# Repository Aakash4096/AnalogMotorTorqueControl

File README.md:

# Zine Project
## Stage 0:
Downloading application such as KiCAD for designing ,simulation and PCB development for the whole project
### Before going to project, the terms one should be familiar with

H-Bridge	A configuration of four MOSFETs (Q1–Q4) that allows current through a DC motor to flow in both directions. It’s called an “H-bridge” because the circuit looks like the letter H: the motor forms the crossbar, and the transistors form the legs.
Purpose	Used to control both direction and speed of a DC motor.
Operation Modes	- Forward: Q1 + Q4 ON (current one way)
- Reverse: Q2 + Q3 ON (current opposite way)
- Brake: Both high-side ON or both low-side ON
- Coast: All OFF
Control Method	Controlled via PWM (Pulse Width Modulation) to vary speed, and logic signals to change direction.

------------------------------------------------------

Half-Bridge	A circuit that controls one side (or “leg”) of an H-bridge — it has a high-side switch and a low-side switch.
Half-Bridge Driver IC	A chip that generates proper gate voltages to drive both MOSFETs (one high-side and one low-side) safely. Example: IR2104, IR2101, HIP4081.
Need for a Driver	- The high-side MOSFET’s gate needs a voltage higher than the supply (Vcc) to turn fully ON.
- A bootstrap capacitor provides this extra voltage.
- The driver ensures dead-time (short delay between switching) so both MOSFETs are not ON at the same time (which would cause a short).
Full H-Bridge with Drivers	Two half-bridge driver ICs together make a full H-bridge (one IC controls each motor terminal).

-----------------------------------------------------

High-Side Switch	The transistor (MOSFET) that connects the motor terminal to +Vcc (e.g., Q1, Q3). Must handle full supply voltage. Usually a P-channel MOSFET or an N-channel driven by a bootstrap circuit.
Low-Side Switch	The transistor that connects the motor terminal to GND (e.g., Q2, Q4). Driven directly from a logic gate or driver IC.
Challenge	Driving the high-side switch requires a voltage higher than Vcc, which is why driver ICs are essential.

-----------------------------------------------------------------

Definition	A digital control method where you switch the motor ON and OFF rapidly (hundreds or thousands of times per second). The average voltage seen by the motor determines speed.
Duty Cycle	The ratio of ON time to total period. Higher duty cycle → more average voltage → faster motor speed.
Frequency	Typical values: 5–20 kHz (high enough to avoid audible noise).
Implementation	Generated by a microcontroller (in your case, ATtiny13A) and fed to the driver IC inputs.

--------------------------------------------------------------------------

Bootstrap Capacitor (Cboot)	A capacitor charged to Vcc when the low-side switch is ON. When the high-side turns ON, this stored charge provides the extra gate voltage needed.
Bootstrap Diode (Dboot)	Allows the capacitor to charge when the low-side is ON, but blocks discharge.
Purpose	Enables an N-channel MOSFET to be used as a high-side transistor (better efficiency and lower Rds(on) than P-channel).

----------------------------------------------------------------------------

Dead-Time Control:-

Definition-	A short time delay between turning OFF one MOSFET and turning ON the opposite one in the same leg.
Why Needed-	Prevents both high-side and low-side switches from being ON simultaneously → avoids shoot-through current, which can destroy the transistors.
Implementation-	Usually built-in inside driver IC (like IR2104) or added by microcontroller timing logic.

---------------------------------------------------------------------------

Current Sensing and Torque Control-

Current Sense Resistor (Rshunt)	A small resistor (e.g., 0.1 Ω) placed in series with the motor to measure current.
Voltage Drop = I × R	The voltage across this resistor is proportional to the motor current → proportional to torque.
Analog Amplifier	Amplifies this small voltage for ADC measurement by the microcontroller.
Torque Control	By regulating motor current, you effectively control torque output (since torque ∝ current in DC motors).

--------------------------------------------------------------------------------

Protection Components-

Flyback Diodes (D1–D4)	Protect MOSFETs from voltage spikes due to motor’s inductive load when switching. Sometimes intrinsic in MOSFETs.
TVS Diode	Protects against sudden voltage surges from external power supply.
Fuse	Protects from short circuits or motor stall overcurrent.
Decoupling Capacitors (C1, C2, etc.)	Stabilize power lines and reduce switching noise.

-------------------------------------------------------------------------------------

Microcontroller (ATtiny13A)
Role	Explanation         
PWM Generation	Generates PWM signals for speed control.    
Direction Control	Sends logic signals to change motor direction.    
Current Measurement	Reads current sense signal for torque estimation.          
Feedback / Safety	Optionally can stop or limit current if torque too high.        

## Stage 1 – Circuit Design

### Power Stage – H-Bridge Design(Idea From Other's Project)

Purpose:

The H-Bridge is a power control circuit that lets current flow through a motor in both directions, so the motor can rotate clockwise or anticlockwise.
It also helps control speed and torque when used with PWM (Pulse Width Modulation) signals.

Started learning by watching how other deployed and operated the whole schematics and designing
From youtube :- https://www.youtube.com/watch?  v=4kDMF0SQ0Zg&list=PLJ0HErIq5D2zQIZq9s4L3cUzeMuB7d4Ho&index=2.   

Thus finally implemented it on my own.

#### moving back to our own project -

This project controls a 12 V DC motor using a full H-bridge configuration driven by two IR2104 half-bridge driver ICs.
Each half-bridge controls one side of the motor, allowing forward and reverse motion.
The ATtiny13A microcontroller generates PWM signals that modulate the motor speed, and a current sense resistor provides feedback proportional to motor torque.
The IR2104 drivers handle the high-side gate voltages using bootstrap capacitors, ensuring safe switching and dead-time to prevent shoot-through.
Protection components like flyback diodes, and decoupling capacitors ensure the circuit is robust against noise and overcurrent.

Searched and gone through specifications for my project 
Components used for this project  

-Motor specification=Light
12 V, 0.1 – 0.5 A
≤ 2 A
5–20 kHz

-Q_PMOS as p-MOSFET

-Q_NMOS_GDS as n-MOSFET

-Resistors

-SS34 as 40V 3A Schottky Diode, SMA

-IR2104 as Half-Bridge Driver, 600V, 210/360mA, PDIP-8/SOIC-8

Taking references from project developed in site:
https://www.pcbway.com/blog/technology/A_Standalone_Full_Bridge_DC_Motor_Driver_2c7c2086.html

Added PWM1 and PWM2 inputs from HALF-BRIDGE driver.

Thus my initial phase of project for power supply h bridge schematics looks like this :-

By following this the above reference, i could finally draft my schematics as this which after testing if error occurs ,i will make minute changes and either edit this or will make a new subsection for it

I have made some scahnges by introducing R_shunt for torque measurement in the motor below :- 

Wanted to add amplifier to amplify current but will complicate the circuit more , first check it and if defection is not that much then will use amplifier as well 

### Some changes 

Noiticed that ,for quick switching of mosfet n type is more suitable than p type , hence i replaced earlier used p mosfet with n mosfet in high side as well and as i was giving the power to  gate using mosfet gate driver so i don't need any extra adjustment to the circuit.

## stage 2
Installed LTspice for simulation as i already know a few things of LTspice .

### ATtiny13A pins :-

1	PB5 (PCINT5 / RESET / ADC0 / dW)	This pin is the Reset input. It also doubles as an input for the ADC channel 0, and the debugWIRE (dW) interface if debugWIRE is enabled. Since RESET is shared, careful if you want to use it as I/O. 
components101.com
+1

2	PB3 (PCINT3 / CLKI / ADC3)	General-purpose I/O pin (Port B bit 3) with additional functions: external clock input (CLKI), ADC channel 3, and pin‐change interrupt. 
ww1.microchip.com
+1

3	PB4 (PCINT4 / ADC2)	I/O pin PB4, also ADC channel 2, and pin-change interrupt source 4. 
AllDataSheet

4	GND	Ground reference.

5	PB0 (MOSI / AIN0 / OC0A / PCINT0)	I/O pin PB0. MOSI (for SPI programming), analog comparator positive input (AIN0), Output Compare Match A (OC0A) for Timer/Counter0, pin‐change interrupt 0. 
Utmel
+1

6	PB1 (MISO / AIN1 / OC0B / INT0 / PCINT1)	I/O pin PB1. MISO (for SPI), comparator negative input (AIN1), Output Compare Match B (OC0B), external interrupt INT0, pin change interrupt 1. 
mouser.com
+1

7	PB2 (SCK / ADC1 / T0 / PCINT2)	I/O pin PB2. SPI SCK (for programming), ADC channel 1, Timer/Counter0 external clock input (T0), pin change interrupt 2. 
himalayansolution.com

8	VCC	Supply voltage pin. Ensure within specified limits depending on variant.

-------------------------------------------------------------------------------------------------------------------------

Implemented some of the basic and miniature version of my project to deepen my understanding of the h-bridge practically by knowning the actual amount of 
current flows through the motor , was not that much satisfied as it was not the actual project but miniature . Which looks something like:-

Next, I am adding gate drivers to my project as to get actual result of my circuit and also will changes some quantites / values as i will get stronh hold on this thing.

These are the ouputs which i got , there is some ringing effect as well as my mosfet is not turning on and off as i wanted it to simulate .

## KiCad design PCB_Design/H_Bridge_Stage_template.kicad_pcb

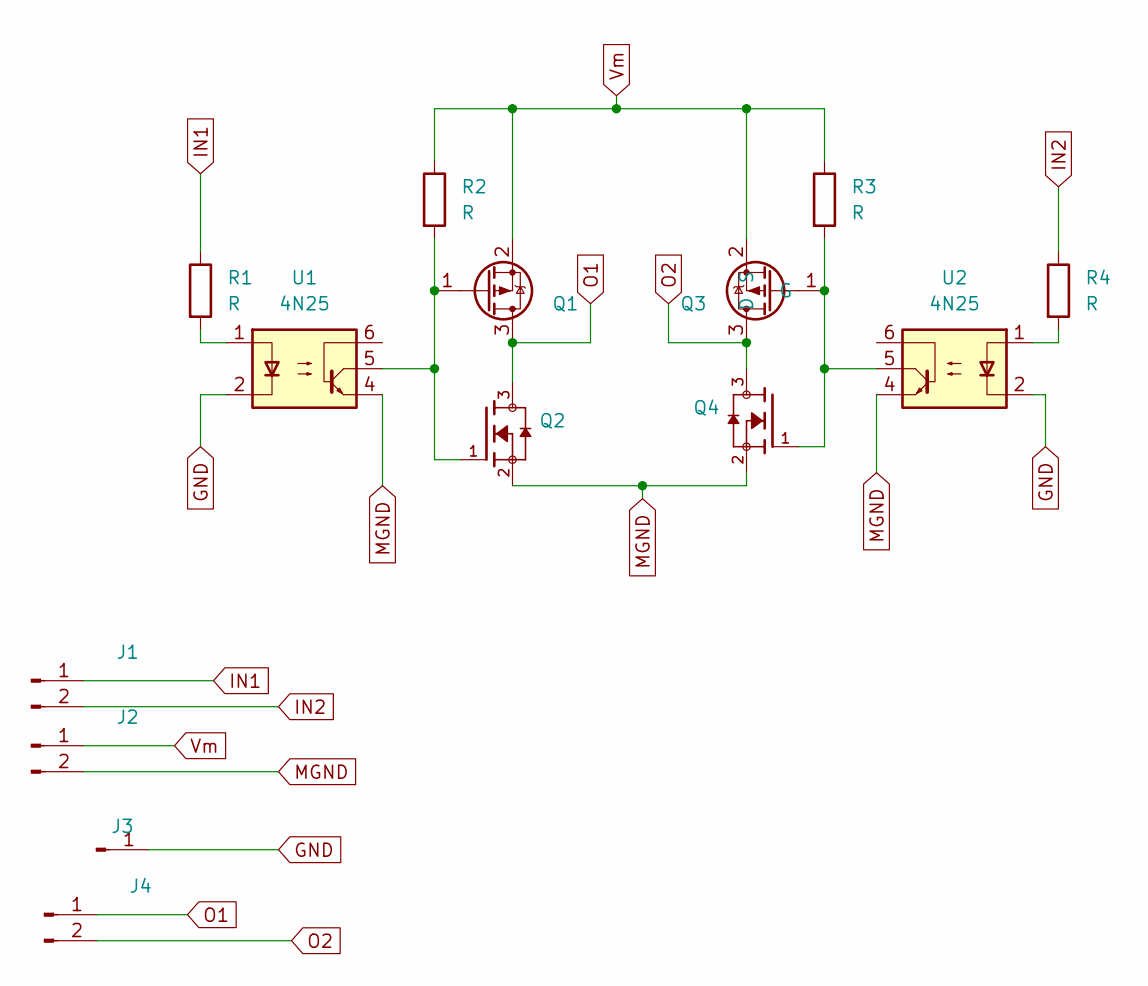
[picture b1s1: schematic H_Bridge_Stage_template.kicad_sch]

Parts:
J1, J2, J4: Conn_01x02_Pin; PinHeader_1x02_P2.54mm_Vertical
J3: Conn_01x01_Pin; PinHeader_1x01_P2.54mm_Vertical
Q1, Q3: AO3401A; SOT-23
Q2, Q4: IRLML6344TRPBF; TRANS_IRLML6344TRPBF; PARTREV December 19, 2014; DigiKey_Part_Number IRLML6344TRPBFCT-ND
R1, R2, R3, R4: R; R_0805_2012Metric_Pad1.20x1.40mm_HandSolder
U1, U2: 4N25; DIP-6_W7.62mm

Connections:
GND: J3.1, U1.2, U2.2
IN1: J1.1, R1.1
IN2: J1.2, R4.1
MGND: J2.2, Q2.2, Q4.2, U1.4, U2.4
unnamed: Q1.1 (G), Q2.1, R2.2, U1.5
unnamed: Q3.1 (G), Q4.1, R3.2, U2.5
unnamed: R1.2, U1.1
unnamed: R4.2, U2.1
O1: J4.1, Q1.3 (D), Q2.3
O2: J4.2, Q3.3 (D), Q4.3
Vm: J2.1, Q1.2 (S), Q3.2 (S), R2.1, R3.1

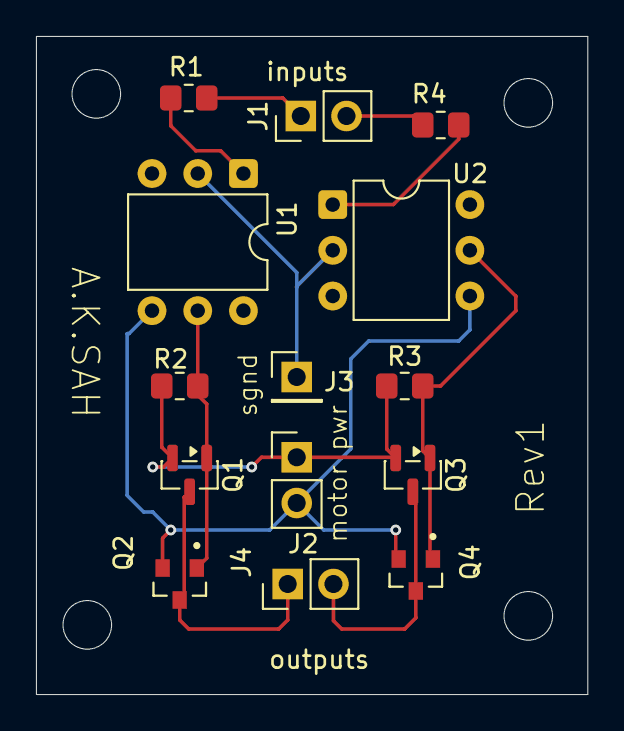
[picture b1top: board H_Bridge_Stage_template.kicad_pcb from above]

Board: 2 copper layers, 30.6 x 36.6 mm, 18 parts (0 on the bottom side), 11 nets.

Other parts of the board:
REF1, REF2, REF3, REF4: MountingHole_2.7mm_M2.5

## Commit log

2025-10-25 Initial commit: Add project files and directory structure
2025-10-26 assets added
2025-10-26 Include schematics image in README
    Add image of schematics to README
2025-10-26 assets updated
2025-10-26 Update README with project parts and resources
    Added sections for project parts and learning resources.
2025-10-26 Fix formatting and spacing in README.md
2025-10-26 Fix formatting and add missing spaces in README
2025-10-26 Revise README with project stages and H-Bridge details
    Updated project stages and added purpose for H-Bridge design.
2025-10-27 Update README with project specifications and components
    Added specifications and components used for the project.
2025-10-27 Update README with project details and components
2025-10-27 minor adjustment in style
2025-10-28 final schematic with KiCAD
2025-10-28 Added new schematics to project by modifying earlier one
2025-10-28 Added some details of term related to project
2025-10-29 minor adjustment
2025-10-29 Revised schematic with KiCAD
2025-10-31 Added picture of latest schematic
2025-10-31 Resolve merge conflicts
2025-10-31 Revise README with project and design information
    Updated the README to include project details, circuit design, and component specifications for the H-Bridge motor control project.
2025-10-31 Revise README with project overview and specifications
    Updated README to include project details, component specifications, and circuit design information.
2025-11-01 Revise README with project details and circuit design
    Updated README to include detailed project information, circuit design, and component specifications for the Zine Project.
2025-11-01 Revise README with project overview and specifications
    Updated README to include project details, circuit design, and component specifications for the H-Bridge motor control project.
2025-11-03 Revise README for Zine Project with detailed updates
    Updated README with detailed project description, components used, and circuit design stages.
2025-11-04 Revise README for H-Bridge motor control project
    Updated README with project details, circuit design, and component specifications for the H-Bridge motor control project.
